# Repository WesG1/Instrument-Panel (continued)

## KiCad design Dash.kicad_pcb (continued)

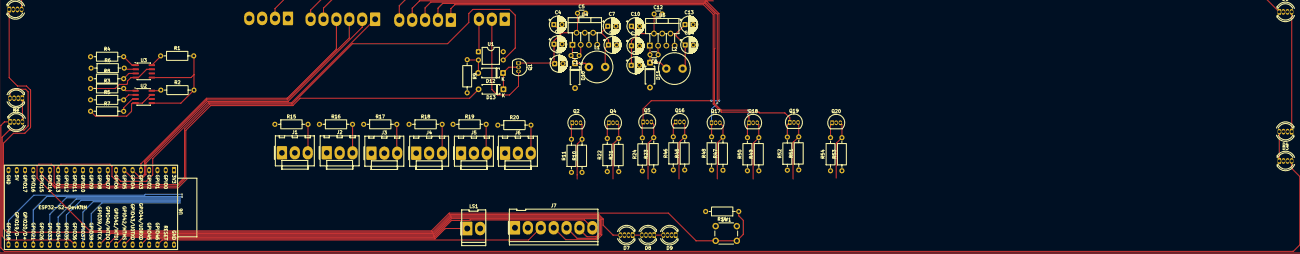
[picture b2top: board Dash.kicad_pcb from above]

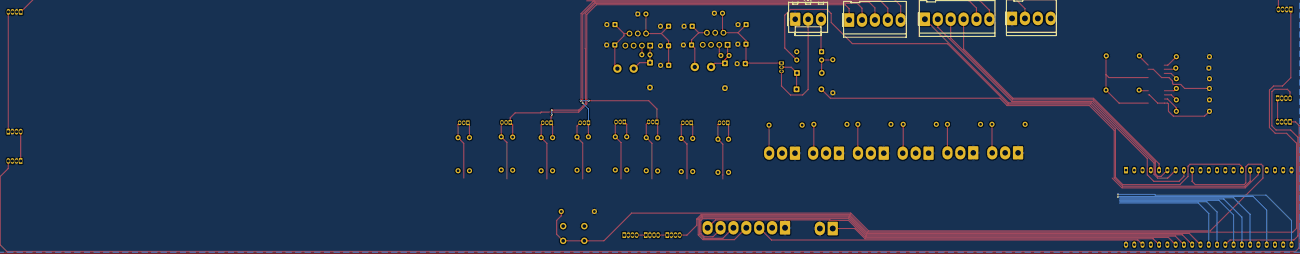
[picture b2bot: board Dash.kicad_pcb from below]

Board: 4 copper layers, 89 parts (4 on the bottom side), 70 nets.

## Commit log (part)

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2026-01-27 Create instrument_panel_code_esp32.ino
    Add project code
2026-01-27 Created schematic branch
    added initial KiCAD schematic and PCB files
2026-02-03 Initial commit for test bench
    A separate circuit to generate sensor signals and light switches
2026-02-10 defined pins
    Added pins to detect headlight activation and pins to detect switched power to unit and control constant power
2026-02-12 Update instrument_panel_code_esp32.ino
    Added comments to clarify parts used and the reserved addresses for those parts. And defined second second i2c driver for LEDs
2026-02-17 Updated schematics
    Added power, logic conversion, eeprom, and other components
2026-02-18 Uploaded correct versions
    uploading correct versions of schematics
2026-02-24 added components
    added power flags, servo connectors, optocoupler, and mosfet
2026-02-25 update
    added more parts to schematic
2026-02-25 update
    added parts to schematic, added pin definitions in code
2026-03-04 Removed PCA chips
    removed pca chips, added additional parts, moved leds to single bus
2026-03-04 update 3/3/26
2026-03-04 Added note, removed extra files
    Added note to change code to reflect hard changes. Removed extra PCB and schematic file
2026-03-04 Second Update
    Added inputs for turn and brake lights, fixed pin positions, added connector for lights and power
2026-03-04 Updated Components
    Changed logic shifter circuit, added logic shifters for lights
2026-03-04 fixed misplaced file
2026-03-10 Update
    Changed logic shifters back to older version, changed names of outputs for clarification, added shifter for echo pin
2026-03-11 Fix after computer crash
2026-03-11 Edited power shut off components
    Placed diodes on gate of power shut off mosfet, one wired to esp32, other wired to keyed power detection
2026-03-12 Updated code
    Updated code to reflect current changes in schematic
2026-03-12 Fixed file location
2026-03-12 added servo attachments
2026-03-19 added note for voltage divider values
    added note for voltage divider values, r1=39k, r2=10k
2026-04-01 Update instrument_panel_code_esp32.ino
    Changed pot variables to sense.
    Added values for voltage divider code.
    Changed servo code to not use PCA chips.
    Added sensor calibration charts.
2026-04-02 file cleanup
2026-04-02 Added missing pin assignments
    Added pins for echo and trigger. Added pin for LED data. Deleted second speaker pin
2026-04-02 Fix errors
    Removed duplicate code. Fixed pin assignments
2026-04-02 Fixed pin assignments
2026-04-03 Update instrument_panel_code_esp32.ino
    Fixed errors, noted Volts function needs rewrite
2026-04-08 Added components
2026-04-08 fixed file locations
2026-04-08 updated pins/variables
    Removed fog light code. Changed pin names for clarity. Reassigned pin position for correct PWM output
2026-04-08 update to correct verison
2026-04-13 Initial Commit
    Created test files for the gauge face for 3D printing
2026-04-14 Started prototype PCB layout
2026-04-14 Update comments
    removed old code. added comments to functions that need to be written
2026-04-16 Added function templates
    Added templates for display, and fault detection functions. Deleted unused function. Added mileage variables
2026-05-11 pin update
    Updated pin assignments
2026-06-04 Update instrument_panel_code_esp32.ino
    Changed code to use rtos instead of super loop format
2026-06-23 added components
    Added additional components
2026-06-26 Update Schematic
    Reverted to older logic shifter design. Added single stage amplifier. Added voltage dividers for gauges.
2026-06-29 Update test bench.kicad_sch
    changed arduinos to esp32
